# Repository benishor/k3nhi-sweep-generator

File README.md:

# k3nhi-sweep-generator
K3NHI sweep generator in KiCad

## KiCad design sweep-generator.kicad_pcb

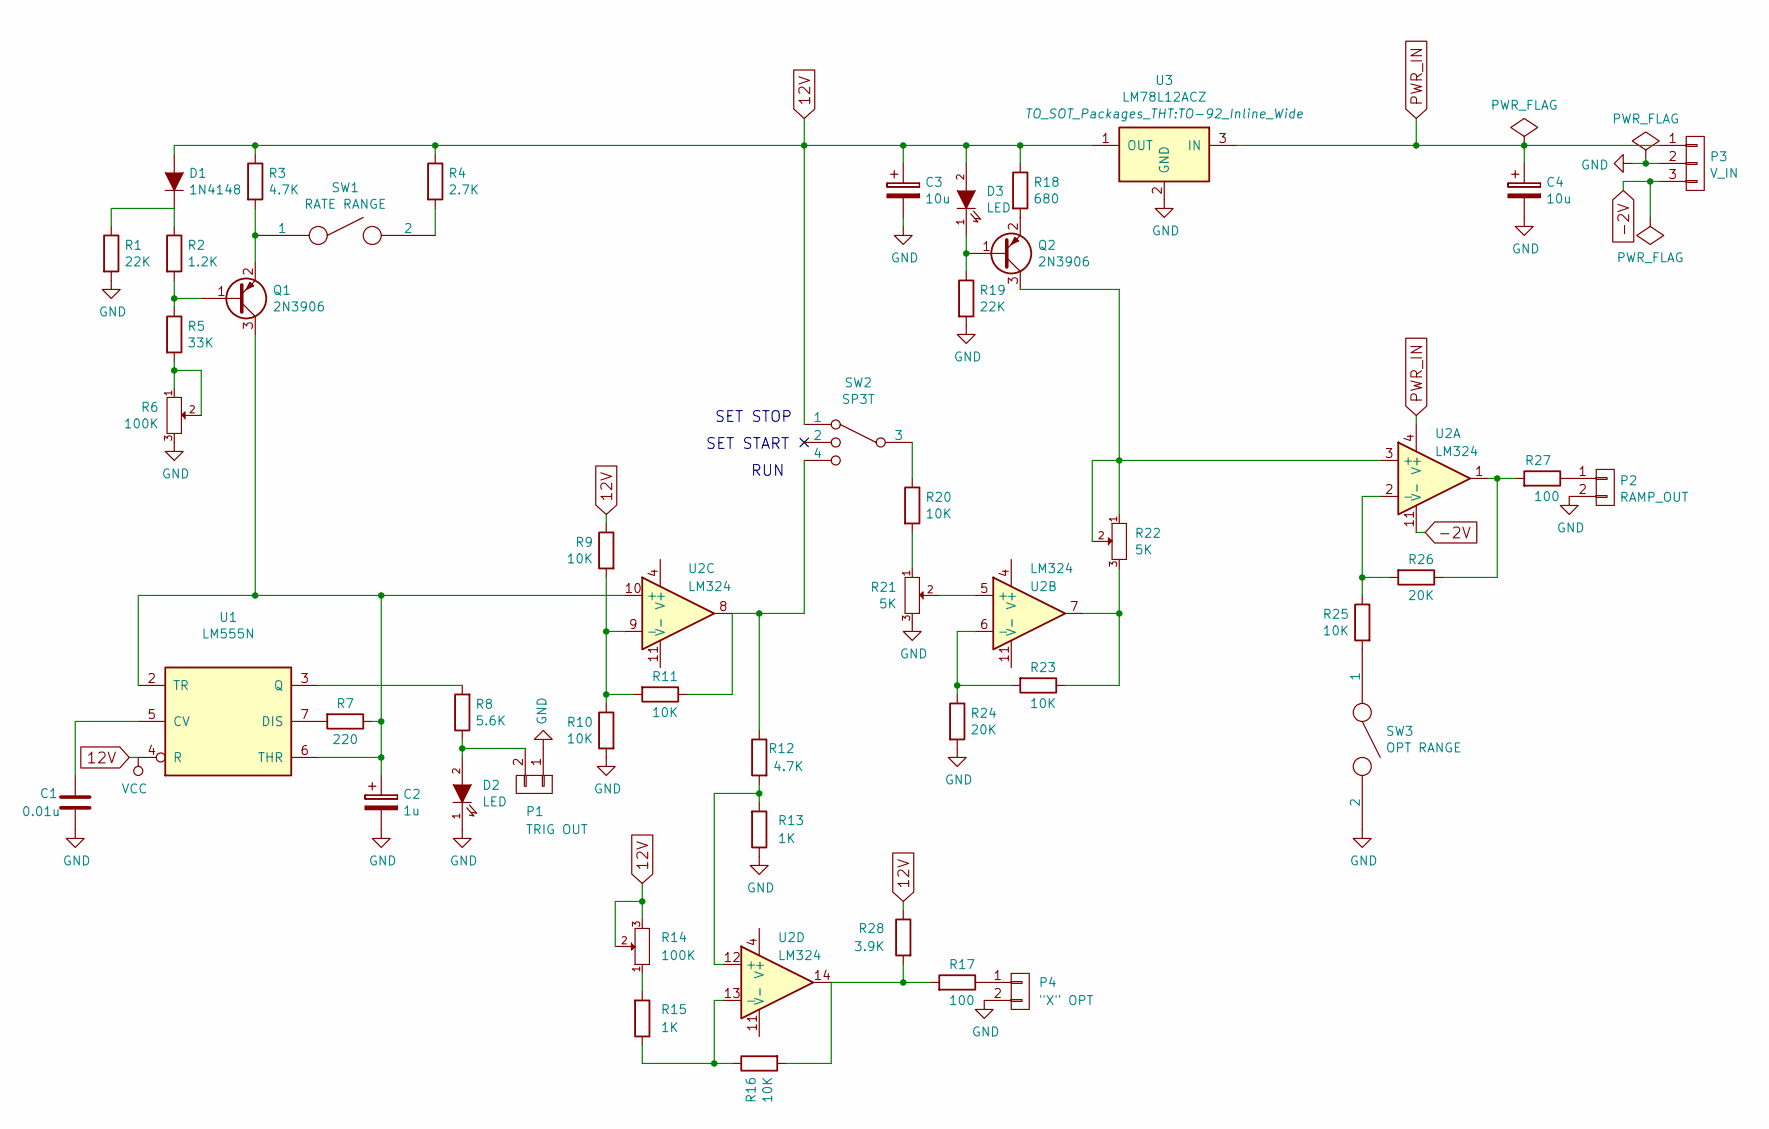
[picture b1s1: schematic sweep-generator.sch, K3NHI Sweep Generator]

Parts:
C1: 0.01u; C_Disc_D6_P5
C2: 1u; C_Radial_D5_L6_P2.5
C3, C4: 10u; C_Radial_D6.3_L11.2_P2.5
D1: 1N4148; Diode_DO-35_SOD27_Horizontal_RM10
D2, D3: LED; LED-3MM
P1: TRIG OUT; Pin_Header_Straight_1x02
P2: RAMP_OUT; Pin_Header_Straight_1x02
P3: V_IN; Pin_Header_Straight_1x03
P4: \"X\" OPT; Pin_Header_Straight_1x02
Q1, Q2: 2N3906; TO-92_Molded_Wide
R1, R19: 22K; Resistor_Horizontal_RM10mm
R2: 1.2K; Resistor_Horizontal_RM10mm
R3, R12: 4.7K; Resistor_Horizontal_RM10mm
R4: 2.7K; Resistor_Horizontal_RM10mm
R5: 33K; Resistor_Horizontal_RM10mm
R6: 100K; Pin_Header_Straight_1x03
R7: 220; Resistor_Horizontal_RM10mm
R8: 5.6K; Resistor_Horizontal_RM10mm
R9, R10, R11, R16, R20, R23, R25: 10K; Resistor_Horizontal_RM10mm
R13, R15: 1K; Resistor_Horizontal_RM10mm
R14: 100K; Potentiometer_Trimmer-Piher-PT15-h5_vertical
R17, R27: 100; Resistor_Horizontal_RM10mm
R18: 680; Resistor_Horizontal_RM10mm
R21, R22: 5K; Pin_Header_Straight_1x03
R24, R26: 20K; Resistor_Horizontal_RM10mm
R28: 3.9K; Resistor_Horizontal_RM10mm
SW1: RATE RANGE; Pin_Header_Straight_1x02
SW2: SP3T; Pin_Header_Straight_1x04
SW3: OPT RANGE; Pin_Header_Straight_1x02
U1: LM555N; DIP-8_W7.62mm_LongPads
U2: LM324; DIP-14_W7.62mm_LongPads
U3: LM78L12ACZ; TO-92_Inline_Wide

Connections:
12V: C3.1, D1.2 (A), D3.2 (A), R3.1, R4.1, R9.1, R14.2, R14.3, R18.1, R28.1, SW2.1, U1.4 (R), U1.8 (VCC), U3.1 (OUT)
-2V: P3.3, U2.11 (V-)
GND: C1.2, C2.2, C3.2, C4.2, D2.1 (K), P1.1, P2.2, P3.2, P4.2, R1.2, R6.3, R10.2, R13.1, R19.2, R21.3, R24.2, SW3.2, U1.1 (GND), U3.2 (GND)
unnamed: C1.1, U1.5 (CV)
unnamed: C2.1, Q1.3 (C), R7.1, U1.2 (TR), U1.6 (THR), U2.10 (+)
unnamed: D1.1 (K), R1.1, R2.1
unnamed: D2.2 (A), P1.2, R8.1
unnamed: D3.1 (K), Q2.1 (B), R19.1
unnamed: P2.1, R27.1
unnamed: P4.1, R17.1
unnamed: Q1.1 (B), R2.2, R5.1
unnamed: Q1.2 (E), R3.2, SW1.1
unnamed: Q2.2 (E), R18.2
unnamed: Q2.3 (C), R22.1, R22.2, U2.3 (+)
unnamed: R4.2, SW1.2
unnamed: R5.2, R6.1, R6.2
unnamed: R7.2, U1.7 (DIS)
unnamed: R8.2, U1.3 (Q)
unnamed: R9.2, R10.1, R11.2, U2.9 (-)
unnamed: R11.1, R12.1, SW2.4, U2.8
unnamed: R12.2, R13.2, U2.12 (+)
unnamed: R14.1, R15.2
unnamed: R15.1, R16.1, U2.13 (-)
unnamed: R16.2, R17.2, R28.2, U2.14
unnamed: R20.1, SW2.3
unnamed: R20.2, R21.1
unnamed: R21.2, U2.5 (+)
unnamed: R22.3, R23.1, U2.7
unnamed: R23.2, R24.1, U2.6 (-)
unnamed: R25.1, R26.2, U2.2 (-)
unnamed: R25.2, SW3.1
unnamed: R26.1, R27.2, U2.1
PWR_IN: C4.1, P3.1, U2.4 (V+), U3.3 (IN)

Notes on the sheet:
SET STOP
SET START
RUN

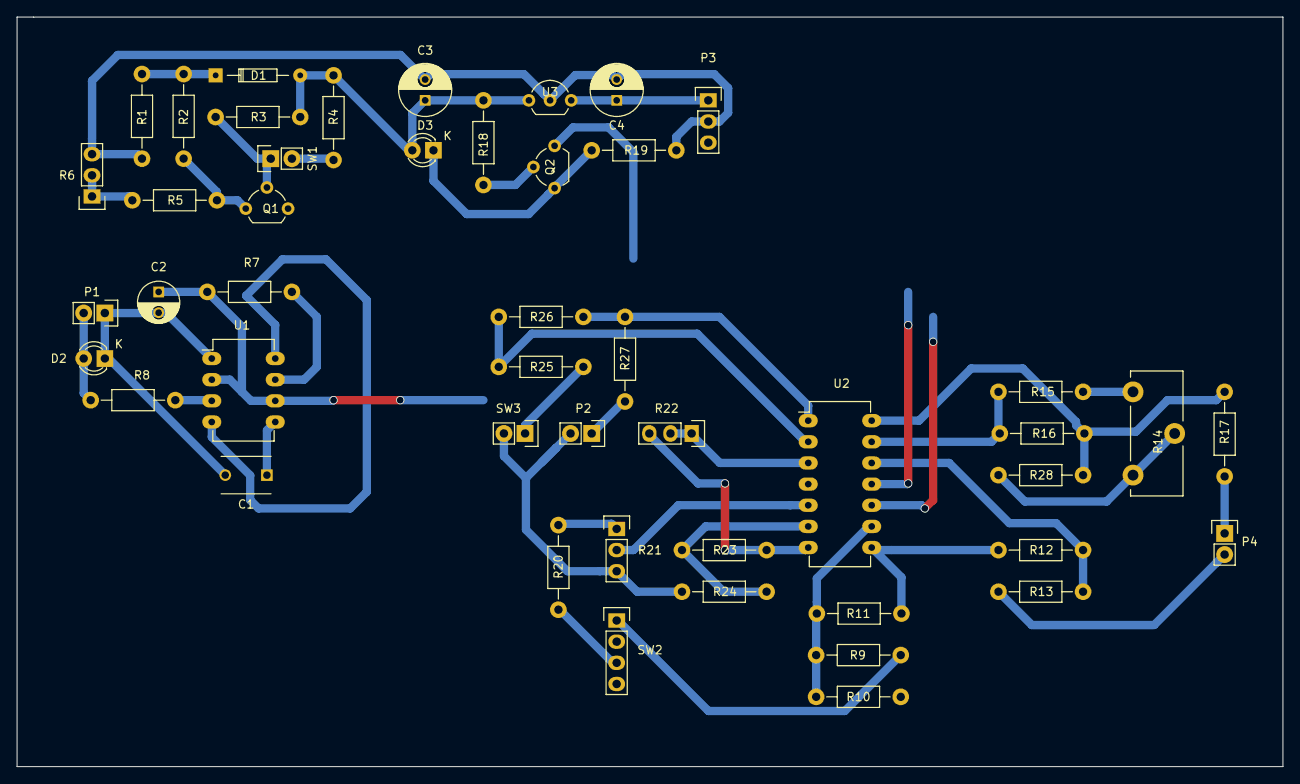
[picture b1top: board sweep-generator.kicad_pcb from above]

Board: 2 copper layers, 152.0 x 90.0 mm, 47 parts (0 on the bottom side), 33 nets.

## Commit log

2016-10-09 Initial import. Through hole version, schematic captured, PCB is WIP.
